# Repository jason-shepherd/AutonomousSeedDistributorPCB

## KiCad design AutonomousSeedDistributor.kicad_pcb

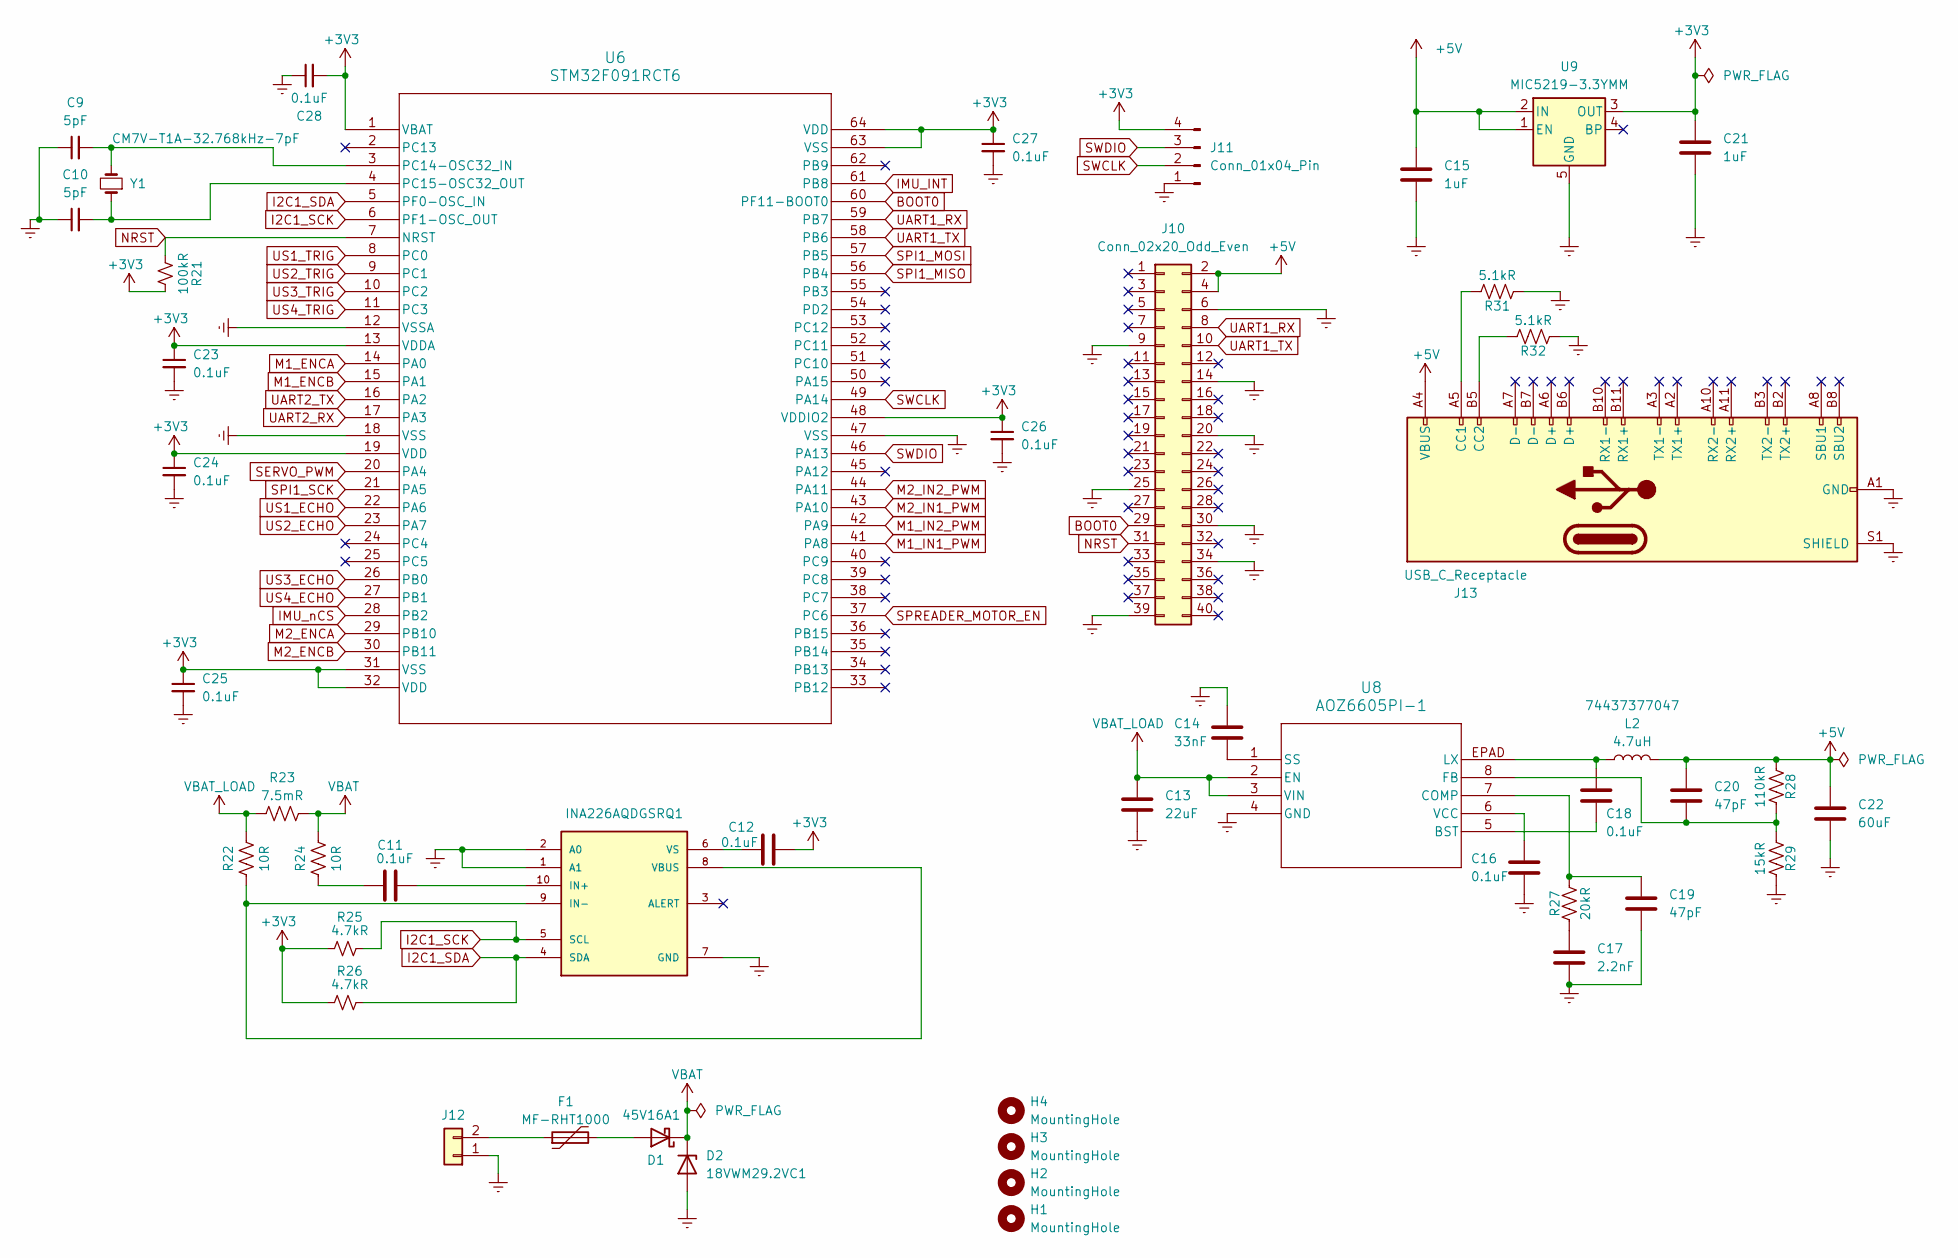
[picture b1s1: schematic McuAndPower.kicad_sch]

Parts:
C9, C10: 5pF; C_0603_1608Metric
C11, C12, C16, C18, C23, C24, C25, C26, C27, C28: 0.1uF; C_0603_1608Metric
C13: 22uF; C_0603_1608Metric
C14: 33nF; C_0603_1608Metric
C15, C21: 1uF; C_0603_1608Metric
C17: 2.2nF; C_0603_1608Metric
C19, C20: 47pF; C_0603_1608Metric
C22: 60uF; C_0603_1608Metric
D1: 45V16A1; TO-220-2_Vertical
D2: 18VWM29.2VC1; D_SOD-123
F1: MF-RHT1000; Fuse_Bourns_MF-RHT1000
H1, H2, H3, H4: MountingHole; MountingHole_2.7mm
J10: Conn_02x20_Odd_Even; PinSocket_2x20_P2.54mm_Vertical
J11: Conn_01x04_Pin; PinHeader_1x04_P2.54mm_Vertical
J12: Battery holes; PHOENIX_1984617
J13: USB_C_Receptacle; USB_C_Receptacle_Amphenol_12401610E4-2A
L2: 4.7uH; WE-LHMI_1335
R21: 100kR; R_0603_1608Metric
R22, R24: 10R; R_0603_1608Metric
R23: 7.5mR; R_2512_6332Metric
R25, R26: 4.7kR; R_0603_1608Metric
R27: 20kR; R_0603_1608Metric
R28: 110kR; R_0603_1608Metric
R29: 15kR; R_0603_1608Metric
R31, R32: 5.1kR; R_0603_1608Metric
U6: STM32F091RCT6; LQFP-64_10x10mm_P0.5mm
U7: INA226AQDGSRQ1; VSSOP-10_3x3mm_P0.5mm
U8: AOZ6605PI-1; SO8_EP1_AOS
U9: MIC5219-3.3YMM; MSOP-8_3x3mm_P0.65mm
Y1: CM7V-T1A-32.768kHz-7pF; Crystal_SMD_3215-2Pin_3.2x1.5mm

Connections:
+3V3: C12.2, C21.1, C23.1, C24.1, C25.1, C26.1, C27.1, C28.2, J11.4, R21.2, R25.1, R26.1, U6.1 (VBAT), U6.13 (VDDA), U6.19 (VDD), U6.31 (VSS), U6.32 (VDD), U6.48 (VDDIO2), U6.63 (VSS), U6.64 (VDD), U9.3 (OUT); also elsewhere on the board
+5V: C15.1, C20.1, C22.1, J10.2, J10.4, J13.A4 (VBUS), J13.A9 (VBUS), J13.B4 (VBUS), J13.B9 (VBUS), L2.2, R28.2, U9.1 (EN), U9.2 (IN); also elsewhere on the board
BOOT0: J10.29, U6.60 (PF11-BOOT0)
GND: C9.1, C10.1, C13.2, C14.1, C15.2, C16.2, C17.2, C19.2, C21.2, C22.2, C23.2, C24.2, C25.2, C26.2, C27.2, C28.1, D2.2 (A), J10.6, J10.9, J10.14, J10.20, J10.25, J10.30, J10.34, J10.39, J11.1, J12.1, J13.A1 (GND), J13.A12 (GND), J13.B1 (GND), J13.B12 (GND), J13.S1 (SHIELD), R29.1, R31.2, R32.2, U6.12 (VSSA), U6.18 (VSS), U6.47 (VSS), U7.1 (A1), U7.2 (A0), U7.7 (GND), U8.4 (GND), U9.5 (GND), U9.6 (GND), U9.7 (GND), U9.8 (GND); also elsewhere on the board
I2C1_SCK: R25.2, U6.6 (PF1-OSC_OUT), U7.5 (SCL)
I2C1_SDA: R26.2, U6.5 (PF0-OSC_IN), U7.4 (SDA)
IMU_INT: U6.61 (PB8); also elsewhere on the board
IMU_nCS: U6.28 (PB2); also elsewhere on the board
M1_ENCA: U6.14 (PA0); also elsewhere on the board
M1_ENCB: U6.15 (PA1); also elsewhere on the board
M1_IN1_PWM: U6.41 (PA8); also elsewhere on the board
M1_IN2_PWM: U6.42 (PA9); also elsewhere on the board
M2_ENCA: U6.29 (PB10); also elsewhere on the board
M2_ENCB: U6.30 (PB11); also elsewhere on the board
M2_IN1_PWM: U6.43 (PA10); also elsewhere on the board
M2_IN2_PWM: U6.44 (PA11); also elsewhere on the board
NRST: J10.31, R21.1, U6.7 (NRST)
unnamed: C11.1, R24.1
unnamed: C17.1, R27.2
unnamed: D1.2 (A), F1.2
unnamed: F1.1, J12.2
unnamed: J13.A5 (CC1), R31.1
unnamed: J13.B5 (CC2), R32.1
unnamed: C9.2, U6.3 (PC14-OSC32_IN), Y1.2
unnamed: C10.2, U6.4 (PC15-OSC32_OUT), Y1.1
unnamed: C11.2, U7.10 (IN+)
unnamed: R22.1, U7.8 (VBUS), U7.9 (IN-)
unnamed: C12.1, U7.6 (VS)
unnamed: C18.2, U8.5 (BST)
unnamed: C19.1, R27.1, U8.7 (COMP)
unnamed: C20.2, R28.1, R29.2, U8.8 (FB)
unnamed: C18.1, L2.1, U8.EPAD (LX)
unnamed: C14.2, U8.1 (SS)
unnamed: C16.1, U8.6 (VCC)
SERVO_PWM: U6.20 (PA4); also elsewhere on the board
SPI1_MISO: U6.56 (PB4); also elsewhere on the board
SPI1_MOSI: U6.57 (PB5); also elsewhere on the board
SPI1_SCK: U6.21 (PA5); also elsewhere on the board
SPREADER_MOTOR_EN: U6.37 (PC6); also elsewhere on the board
SWCLK: J11.2, U6.49 (PA14)
SWDIO: J11.3, U6.46 (PA13)
UART1_RX: J10.8, U6.59 (PB7)
UART1_TX: J10.10, U6.58 (PB6)
UART2_RX: U6.17 (PA3); also elsewhere on the board
UART2_TX: U6.16 (PA2); also elsewhere on the board
US1_ECHO: U6.22 (PA6); also elsewhere on the board
US1_TRIG: U6.8 (PC0); also elsewhere on the board
US2_ECHO: U6.23 (PA7); also elsewhere on the board
US2_TRIG: U6.9 (PC1); also elsewhere on the board
US3_ECHO: U6.26 (PB0); also elsewhere on the board
US3_TRIG: U6.10 (PC2); also elsewhere on the board
US4_ECHO: U6.27 (PB1); also elsewhere on the board
US4_TRIG: U6.11 (PC3); also elsewhere on the board
VBAT: D1.1 (K), D2.1 (K), R23.2, R24.2
VBAT_LOAD: C13.1, R22.2, R23.1, U8.2 (EN), U8.3 (VIN); also elsewhere on the board

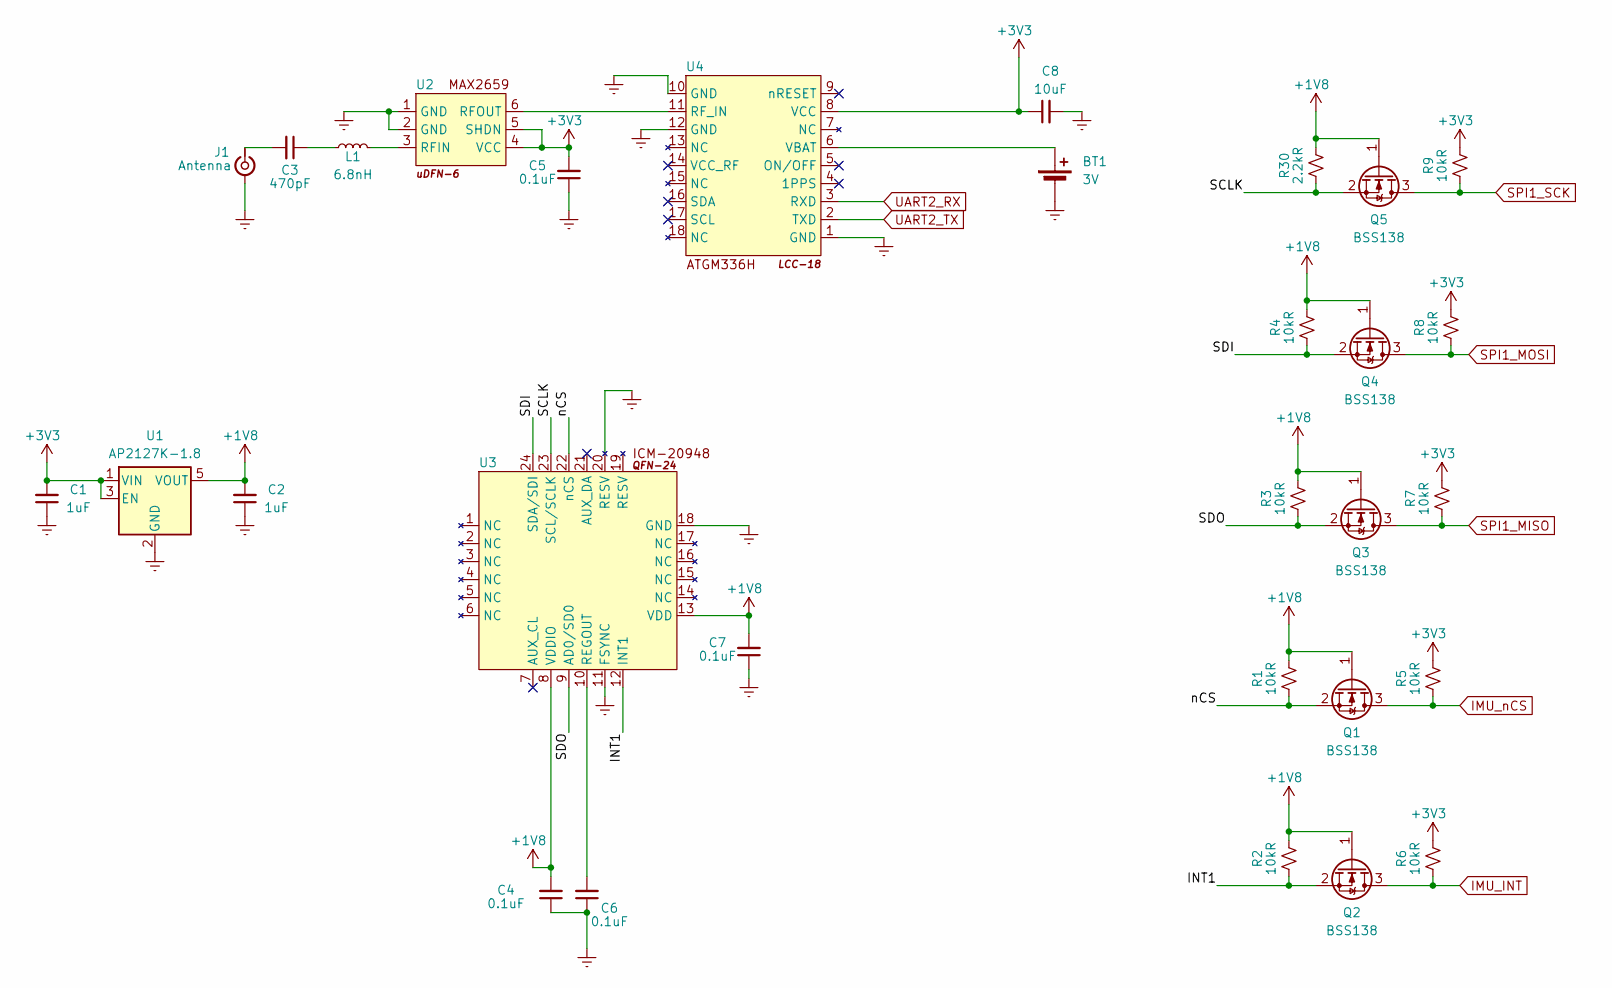
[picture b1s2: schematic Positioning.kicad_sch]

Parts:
BT1: 3V; SEIKO_ML414H_IV01E
C1, C2: 1uF; C_0603_1608Metric
C3: 470pF; C_0603_1608Metric
C4, C5, C6, C7: 0.1uF; C_0603_1608Metric
C8: 10uF; C_0603_1608Metric
J1: Antenna; U.FL_Molex_MCRF_73412-0110_Vertical
L1: 6.8nH; L_0603_1608Metric
Q1, Q2, Q3, Q4, Q5: BSS138; SOT-23
R1, R2, R3, R4, R5, R6, R7, R8, R9: 10kR; R_0603_1608Metric
R30: 2.2kR; R_0603_1608Metric
U1: AP2127K-1.8; SOT-23-5
U2: uDFN-6
U3: QFN-24-1EP_3x3mm_P0.4mm_EP1.75x1.6mm
U4: LCC-18

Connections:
+1V8: C2.2, C4.2, C7.2, Q1.1 (G), Q2.1 (G), Q3.1 (G), Q4.1 (G), Q5.1 (G), R1.2, R2.2, R3.2, R4.2, R30.2, U1.5 (VOUT), U3.8 (VDDIO), U3.13 (VDD)
+3V3: C1.2, C5.2, C8.1, R5.2, R6.2, R7.2, R8.2, R9.2, U1.1 (VIN), U1.3 (EN), U2.4 (VCC), U2.5 (SHDN), U4.8 (VCC); also elsewhere on the board
/Positioning/INT1: Q2.2 (S), R2.1, U3.12 (INT1)
/Positioning/SCLK: Q5.2 (S), R30.1, U3.23 (SCL/SCLK)
/Positioning/SDI: Q4.2 (S), R4.1, U3.24 (SDA/SDI)
/Positioning/SDO: Q3.2 (S), R3.1, U3.9 (AD0/SD0)
/Positioning/nCS: Q1.2 (S), R1.1, U3.22 (nCS)
GND: BT1.2 (-), C1.1, C2.1, C4.1, C5.1, C6.1, C7.1, C8.2, J1.2 (Ext), U1.2 (GND), U2.1 (GND), U2.2 (GND), U3.11 (FSYNC), U3.18 (GND), U3.20 (RESV), U4.1 (GND), U4.10 (GND), U4.12 (GND); also elsewhere on the board
IMU_INT: Q2.3 (D), R6.1; also elsewhere on the board
IMU_nCS: Q1.3 (D), R5.1; also elsewhere on the board
unnamed: BT1.1 (+), U4.6 (VBAT)
unnamed: C3.1, L1.1
unnamed: C3.2, J1.1 (In)
unnamed: L1.2, U2.3 (RFIN)
unnamed: U2.6 (RFOUT), U4.11 (RF_IN)
unnamed: C6.2, U3.10 (REGOUT)
SPI1_MISO: Q3.3 (D), R7.1; also elsewhere on the board
SPI1_MOSI: Q4.3 (D), R8.1; also elsewhere on the board
SPI1_SCK: Q5.3 (D), R9.1; also elsewhere on the board
UART2_RX: U4.3 (RXD); also elsewhere on the board
UART2_TX: U4.2 (TXD); also elsewhere on the board

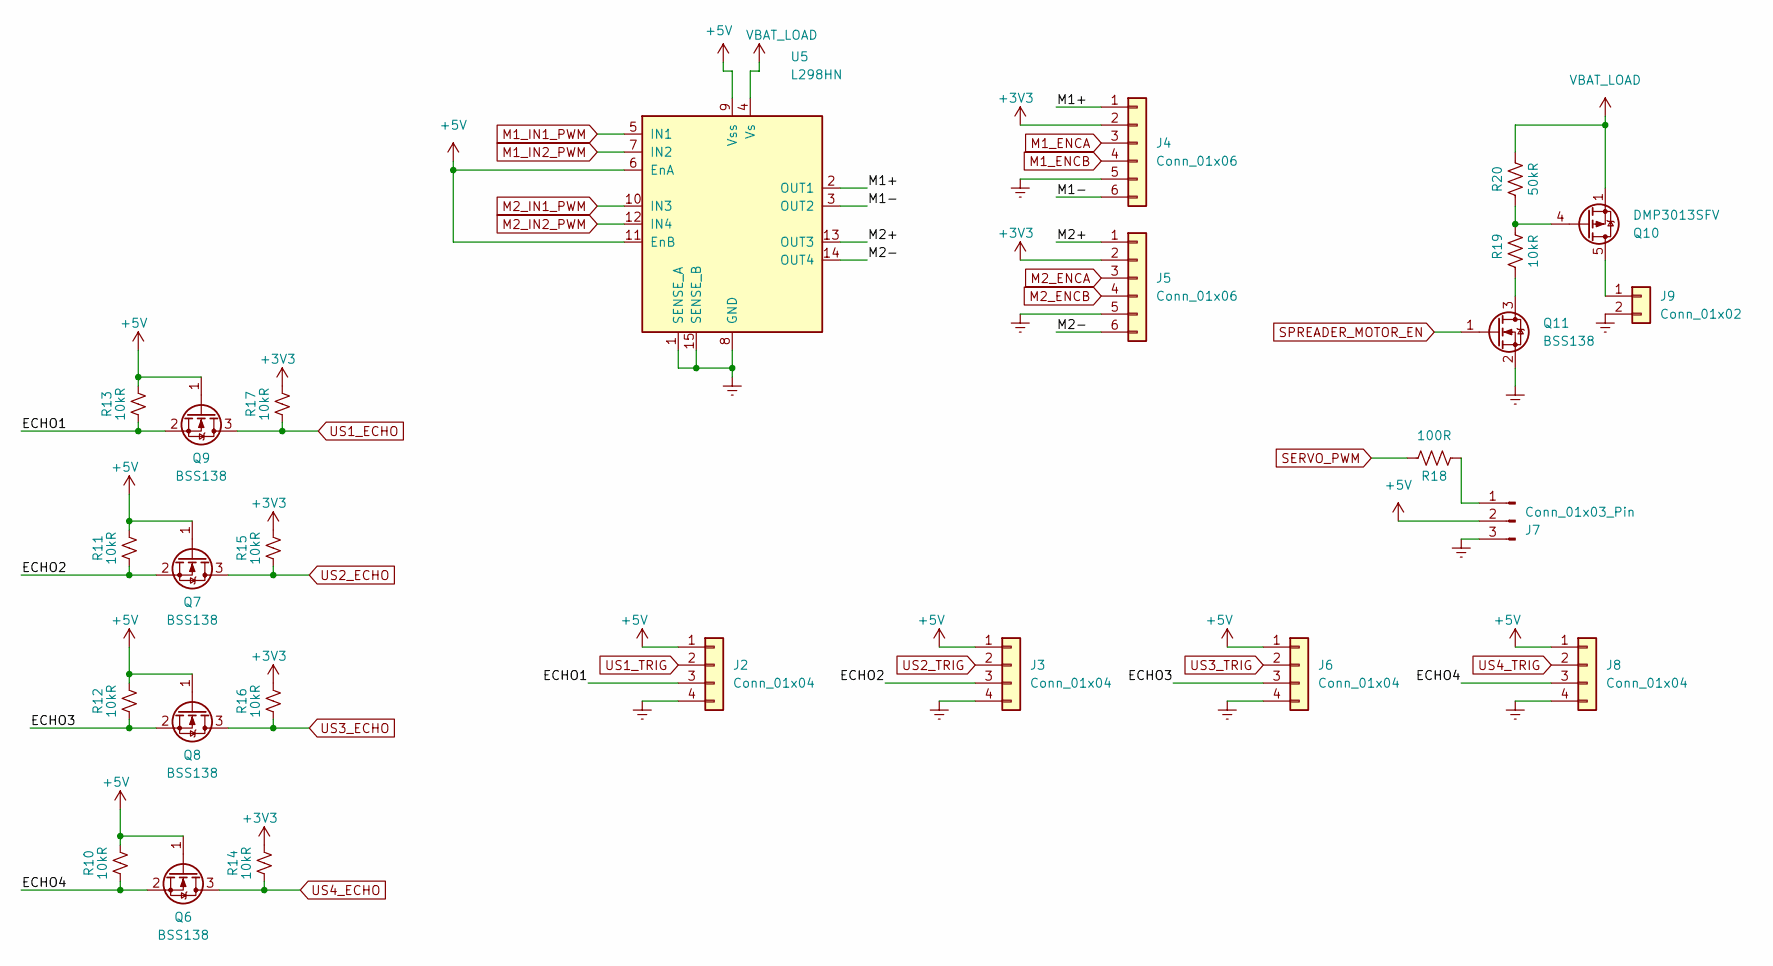
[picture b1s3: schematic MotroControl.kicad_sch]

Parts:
J2, J3, J6, J8: Conn_01x04; PinHeader_1x04_P2.54mm_Vertical
J4, J5: Conn_01x06; JST_PH_B6B-PH-K_1x06_P2.00mm_Vertical
J7: Conn_01x03_Pin; PinHeader_1x03_P2.54mm_Vertical
J9: Conn_01x02; PHOENIX_1984617
Q6, Q7, Q8, Q9, Q11: BSS138; SOT-23
Q10: DMP3013SFV; Diodes_PowerDI3333-8
R10, R11, R12, R13, R14, R15, R16, R17, R19: 10kR; R_0603_1608Metric
R18: 100R; R_0603_1608Metric
R20: 50kR; R_0603_1608Metric
U5: L298HN; TO-220-15_P2.54x2.54mm_StaggerOdd_Lead5.84mm_TabDown

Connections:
+3V3: J4.2, J5.2, R14.2, R15.2, R16.2, R17.2; also elsewhere on the board
+5V: J2.1, J3.1, J6.1, J7.2, J8.1, Q6.1 (G), Q7.1 (G), Q8.1 (G), Q9.1 (G), R10.2, R11.2, R12.2, R13.2, U5.6 (EnA), U5.9 (Vss), U5.11 (EnB); also elsewhere on the board
/Motor Control/ECHO1: J2.3, Q9.2 (S), R13.1
/Motor Control/ECHO2: J3.3, Q7.2 (S), R11.1
/Motor Control/ECHO3: J6.3, Q8.2 (S), R12.1
/Motor Control/ECHO4: J8.3, Q6.2 (S), R10.1
/Motor Control/M1+: J4.1, U5.2 (OUT1)
/Motor Control/M1-: J4.6, U5.3 (OUT2)
/Motor Control/M2+: J5.1, U5.13 (OUT3)
/Motor Control/M2-: J5.6, U5.14 (OUT4)
GND: J2.4, J3.4, J4.5, J5.5, J6.4, J7.3, J8.4, J9.2, Q11.2 (S), U5.1 (SENSE_A), U5.8 (GND), U5.15 (SENSE_B); also elsewhere on the board
M1_ENCA: J4.3; also elsewhere on the board
M1_ENCB: J4.4; also elsewhere on the board
M1_IN1_PWM: U5.5 (IN1); also elsewhere on the board
M1_IN2_PWM: U5.7 (IN2); also elsewhere on the board
M2_ENCA: J5.3; also elsewhere on the board
M2_ENCB: J5.4; also elsewhere on the board
M2_IN1_PWM: U5.10 (IN3); also elsewhere on the board
M2_IN2_PWM: U5.12 (IN4); also elsewhere on the board
unnamed: J7.1, R18.2
unnamed: J9.1, Q10.5 (D)
unnamed: Q10.4 (G), R19.2, R20.2
unnamed: Q11.3 (D), R19.1
SERVO_PWM: R18.1; also elsewhere on the board
SPREADER_MOTOR_EN: Q11.1 (G); also elsewhere on the board
US1_ECHO: Q9.3 (D), R17.1; also elsewhere on the board
US1_TRIG: J2.2; also elsewhere on the board
US2_ECHO: Q7.3 (D), R15.1; also elsewhere on the board
US2_TRIG: J3.2; also elsewhere on the board
US3_ECHO: Q8.3 (D), R16.1; also elsewhere on the board
US3_TRIG: J6.2; also elsewhere on the board
US4_ECHO: Q6.3 (D), R14.1; also elsewhere on the board
US4_TRIG: J8.2; also elsewhere on the board
VBAT_LOAD: Q10.1 (S), Q10.2 (S), Q10.3 (S), R20.1, U5.4 (Vs); also elsewhere on the board

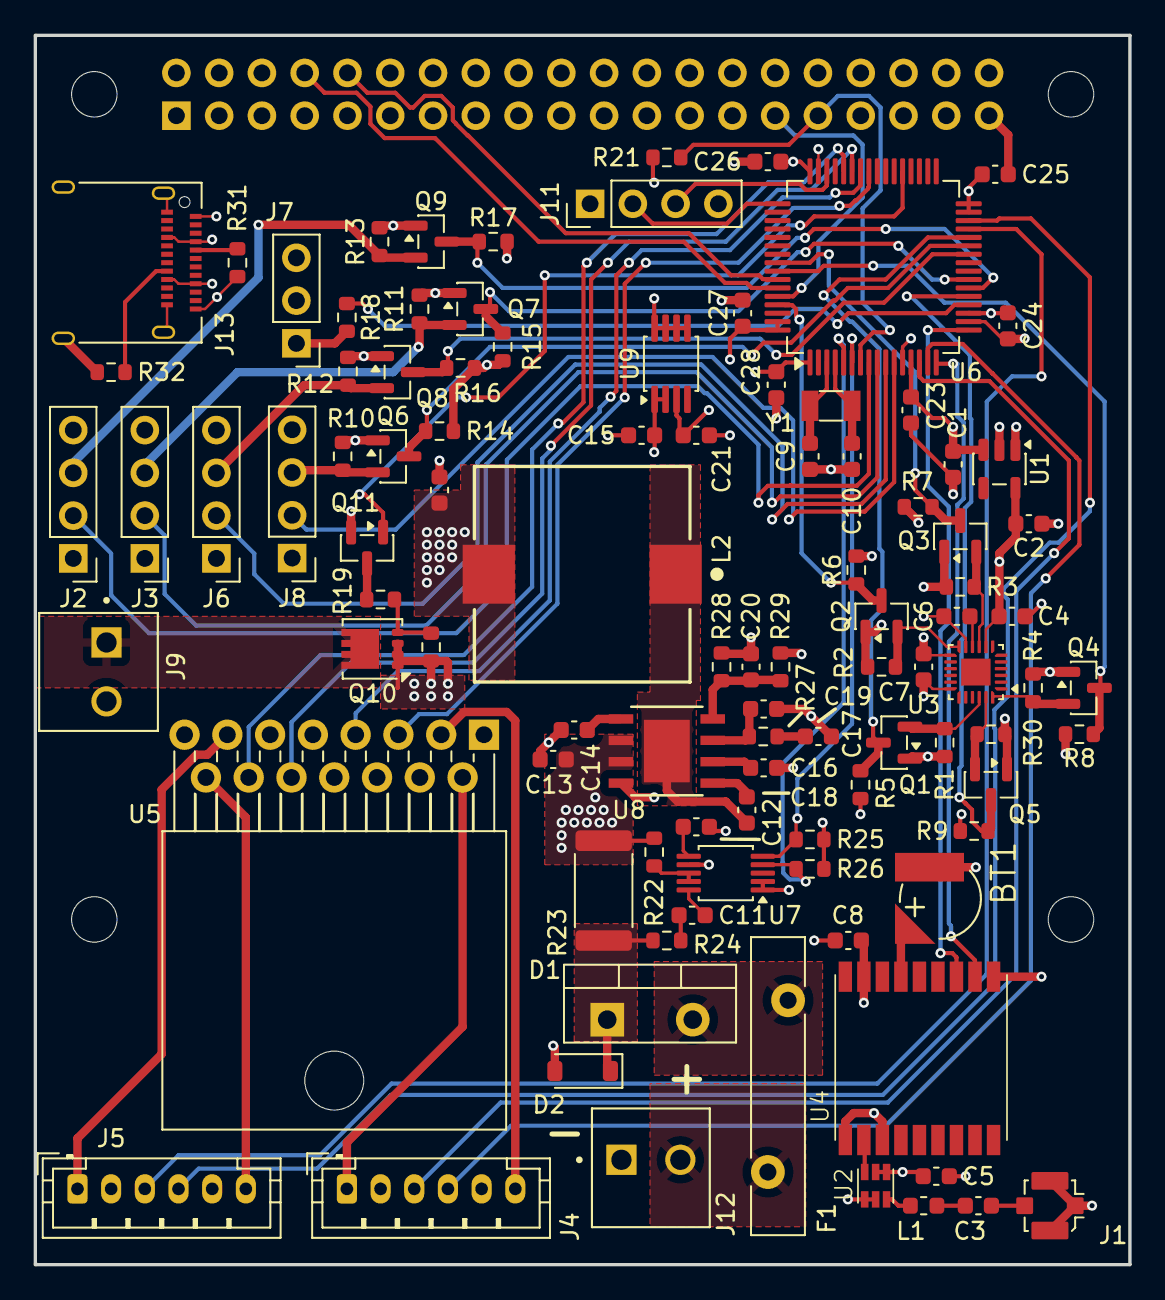
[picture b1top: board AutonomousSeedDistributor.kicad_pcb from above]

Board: 4 copper layers, 65.0 x 73.0 mm, 104 parts (1 on the bottom side), 79 nets.

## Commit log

2025-10-11 CH9121 schematic complete
2025-10-11 schematics for subsystem mostly done
2025-10-11 added logic shifters for IMU
2025-10-12 assigned footprints
2025-10-12 routed besides mcu connections and pwoer
2025-10-13 done with my subsystem
2025-10-13 combined, submitted for Packaging Review
2025-11-17 rev 1
2025-11-17 committed lock by accident
